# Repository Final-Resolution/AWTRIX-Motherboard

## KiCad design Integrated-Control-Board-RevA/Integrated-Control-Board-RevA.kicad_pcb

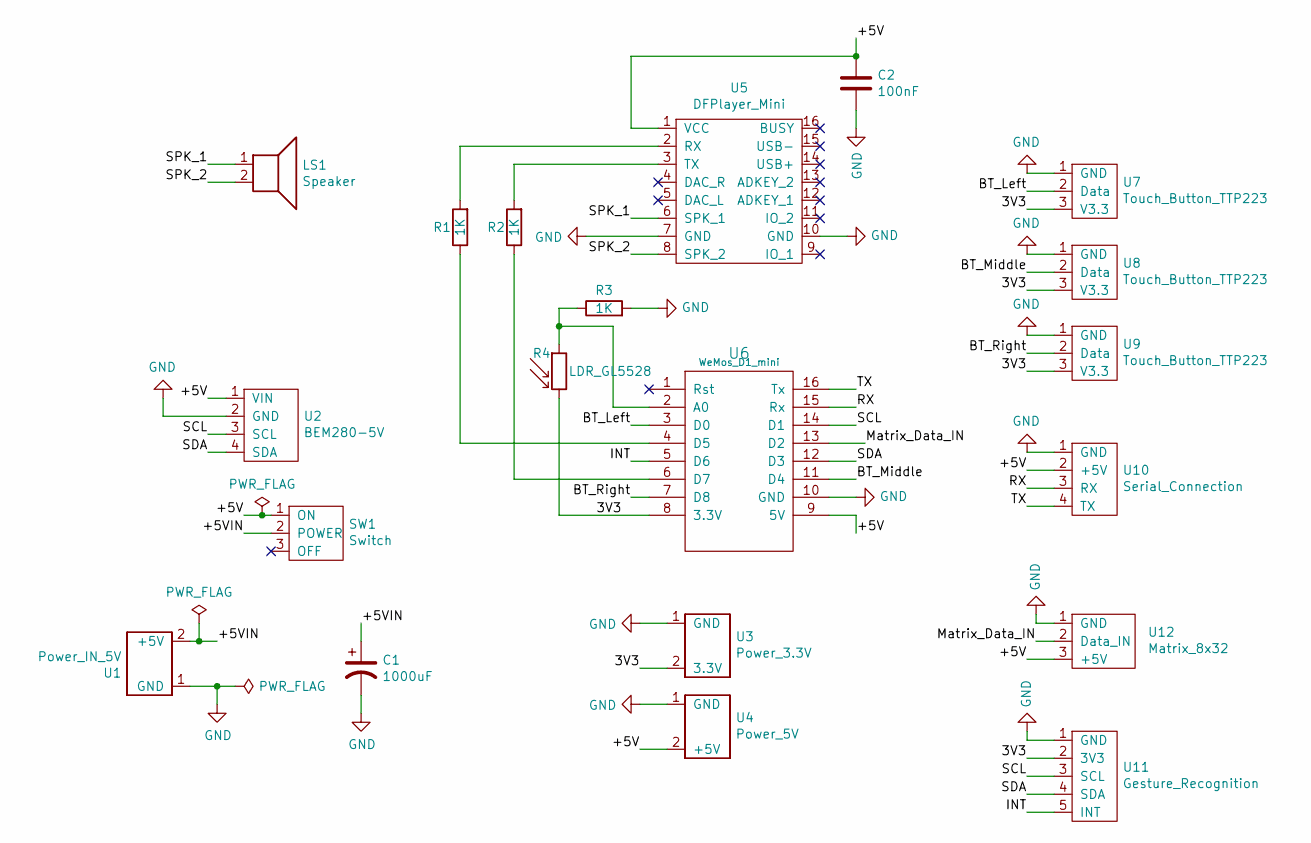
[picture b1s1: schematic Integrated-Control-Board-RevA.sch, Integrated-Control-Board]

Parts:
C1: 1000uF; CP_Radial_D8.0mm_P5.00mm
C2: 100nF; C_Disc_D5.0mm_W2.5mm_P5.00mm
LS1: Speaker; PinHeader_1x02_P2.54mm
R1, R2, R3: 1K; R_Axial_DIN0207_L6.3mm_D2.5mm_P10.16mm_Horizontal
R4: LDR_GL5528; PinHeader_1x02_P2.54mm
SW1: Switch; PinHeader_1x03_P2.54mm
U1: Power_IN_5V; PinHeader_1x02_P2.54mm
U2: BEM280-5V; PinHeader_1x04_P2.54mm
U3: Power_3.3V; PinHeader_1x02_P2.54mm
U4: Power_5V; PinHeader_1x02_P2.54mm
U5: DFPlayer_Mini; DFPlayer
U6: WeMos_D1_mini; wemos-d1-mini-with-pin-header-and-connector
U7, U8, U9: Touch_Button_TTP223; PinHeader_1x03_P2.54mm
U10: Serial_Connection; PinHeader_1x04_P2.54mm
U11: Gesture_Recognition; PinHeader_1x05_P2.54mm
U12: Matrix_8x32; PinHeader_1x03_P2.54mm

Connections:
/3V3: R4.2, U3.2 (3.3V), U6.8 (3.3V), U7.3 (V3.3), U8.3 (V3.3), U9.3 (V3.3), U11.2 (3V3)
/+5V: C2.1, SW1.1 (ON), U2.1 (VIN), U4.2 (+5V), U5.1 (VCC), U6.9 (5V), U10.2 (+5V), U12.3 (+5V)
/+5VIN: C1.1, SW1.2 (POWER), U1.2 (+5V)
/BT_Left: U6.3 (D0), U7.2 (Data)
/BT_Middle: U6.11 (D4), U8.2 (Data)
/BT_Right: U6.7 (D8), U9.2 (Data)
/INT: U6.5 (D6), U11.5 (INT)
/Matrix_Data_IN: U6.13 (D2), U12.2 (Data_IN)
/RX: U6.15 (Rx), U10.3 (RX)
/SCL: U2.3 (SCL), U6.14 (D1), U11.3 (SCL)
/SDA: U2.4 (SDA), U6.12 (D3), U11.4 (SDA)
/SPK_1: LS1.1, U5.6 (SPK_1)
/SPK_2: LS1.2, U5.8 (SPK_2)
/TX: U6.16 (Tx), U10.4 (TX)
GND: C1.2, C2.2, R3.2, U1.1 (GND), U2.2 (GND), U3.1 (GND), U4.1 (GND), U5.7 (GND), U5.10 (GND), U6.10 (GND), U7.1 (GND), U8.1 (GND), U9.1 (GND), U10.1 (GND), U11.1 (GND), U12.1 (GND)
unnamed: R1.1, U6.4 (D5)
unnamed: R1.2, U5.2 (RX)
unnamed: R2.1, U6.6 (D7)
unnamed: R2.2, U5.3 (TX)
unnamed: R3.1, R4.1, U6.2 (A0)

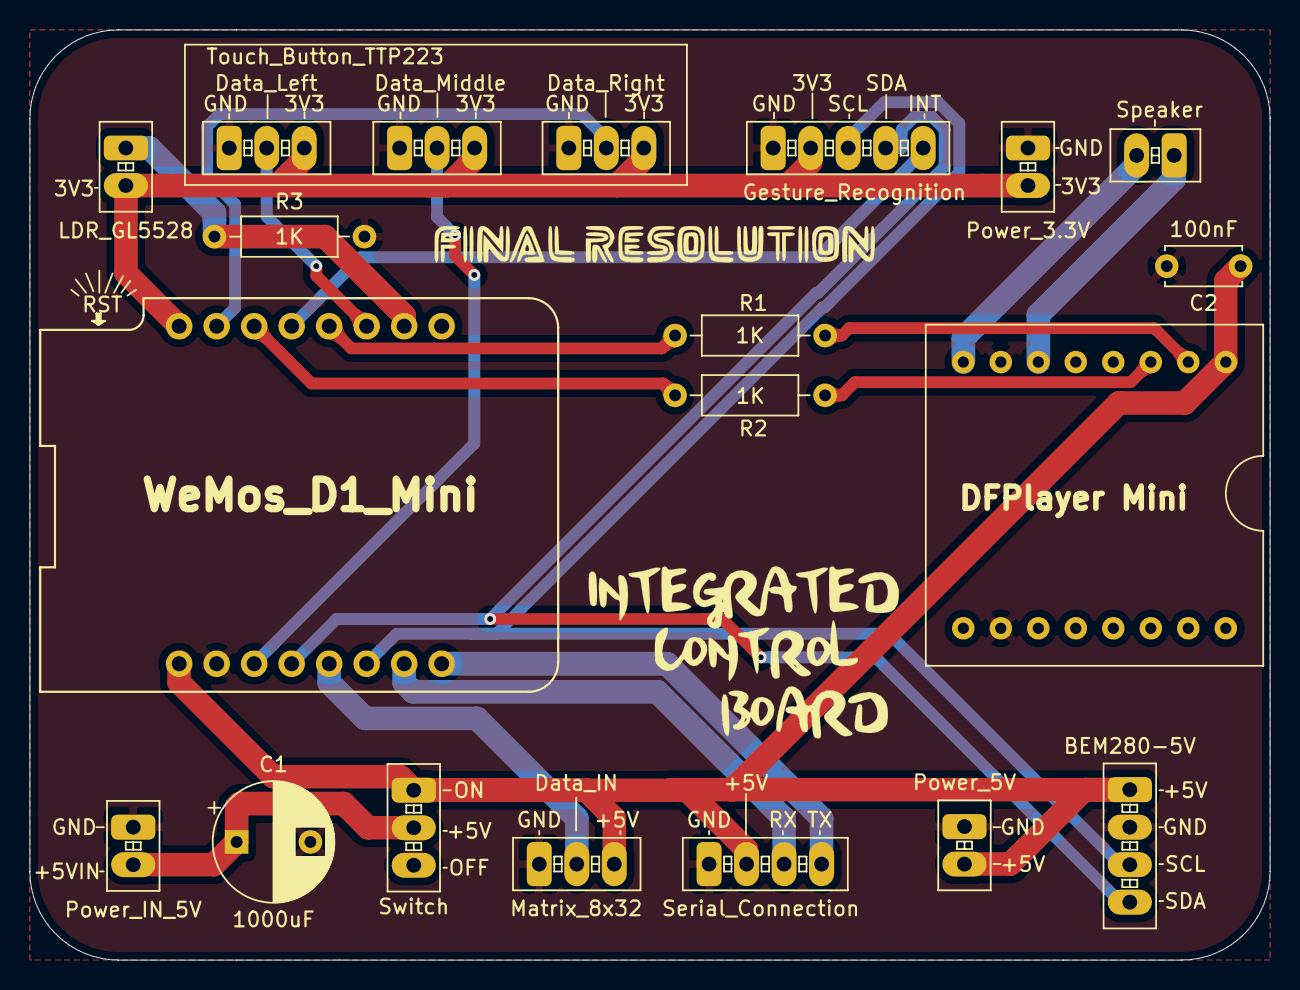
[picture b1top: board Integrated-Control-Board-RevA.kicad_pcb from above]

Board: 2 copper layers, 84.0 x 63.0 mm, 20 parts (0 on the bottom side), 20 nets.
